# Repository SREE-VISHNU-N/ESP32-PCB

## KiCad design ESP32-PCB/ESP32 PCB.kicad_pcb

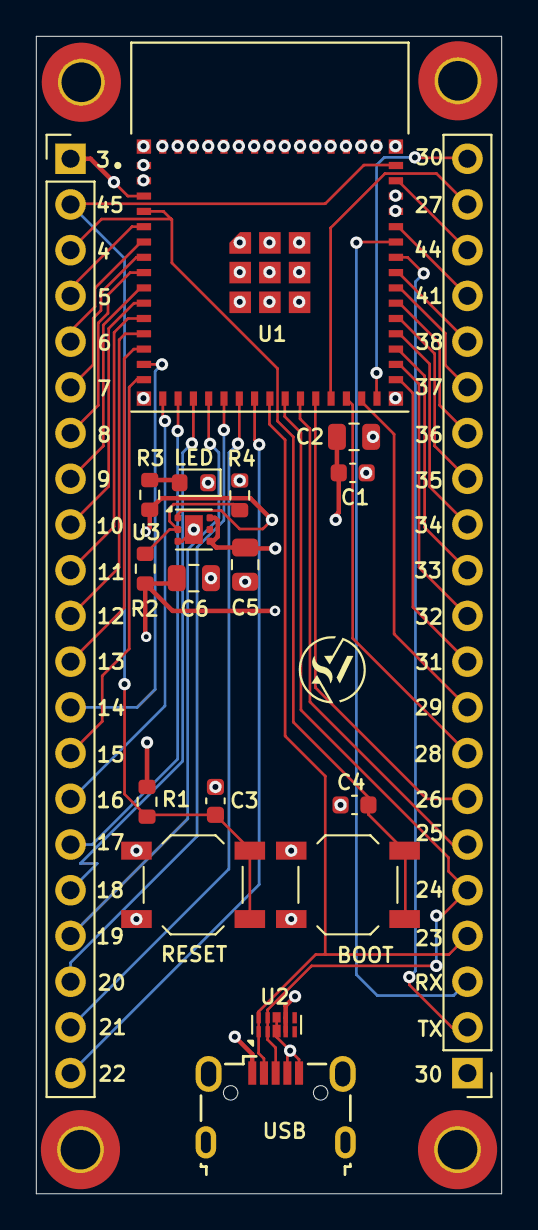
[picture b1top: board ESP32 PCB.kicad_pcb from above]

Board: 4 copper layers, 25.8 x 64.3 mm, 23 parts (0 on the bottom side), 45 nets.

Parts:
C1, C3, C4: 0.1uF; C_0603_1608Metric
C2, C5, C6: 10uF; C_0805_2012Metric
H1, H2, H3, H4: MountingHole_Pad; MountingHole_2.2mm_M2_Pad_TopBottom
J1, J2: Conn_01x21_Pin; PinHeader_1x21_P2.54mm_Vertical
LED: LED; LED_0603_1608Metric
R1: 10k; R_0603_1608Metric
R2: 1M; R_0603_1608Metric
R3: 5.1k; R_0603_1608Metric
R4: 200k; R_0603_1608Metric
RESET: RESET1; SW_SPST_TL3342
SW2: BOOT1; SW_SPST_TL3342
U1: ESP32-S3-MINI-1-N8; XCVR_ESP32-S3-MINI-1-N8
U2: D3V3XA4B10LP; Diodes_UDFN-10_1.0x2.5mm_P0.5mm
U3: TLV75801PDRV; WSON-6-1EP_2x2mm_P0.65mm_EP1x1.6mm
USB : USB_B_Micro; USB_Micro-B_Wuerth_629105150521

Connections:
/3V3: C1.1, C2.1, C6.1, J1.1, R1.1, R2.1, R3.1, U1.3 (3V3), U3.1 (OUT)
/5VUSB: C5.1, U2.4, U2.7 (NC), U3.4 (EN), U3.6 (IN), USB.1 (VBUS)
/EN: C3.1, J1.2, R1.2, RESET.3 (K), RESET.4 (A), U1.45 (EN)
/GP100: C4.1, J1.3, SW2.3 (K), SW2.4 (A), U1.4 (IO0)
/GP101: J1.4, U1.5 (IO1)
/GP102: J1.5, U1.6 (IO2)
/GP103: J1.6, U1.7 (IO3)
/GP104: J1.7, U1.8 (IO4)
/GP105: J1.8, U1.9 (IO5)
/GP106: J1.9, U1.10 (IO6)
/GP107: J1.10, U1.11 (IO7)
/GP108: J1.11, U1.12 (IO8)
/GP109: J1.12, U1.13 (IO9)
/GP1010: J1.13, U1.14 (IO10)
/GP1011: J1.14, U1.15 (IO11)
/GP1012: J1.15, U1.16 (IO12)
/GP1013: J1.16, U1.17 (IO13)
/GP1014: J1.17, U1.18 (IO14)
/GP1015: J1.18, U1.19 (IO15)
/GP1016: J1.19, U1.20 (IO16)
/GP1017: J1.20, U1.21 (IO17)
/GP1018: J1.21, U1.22 (IO18)
/GP1019: J2.4, U1.23 (IO19), U2.1, U2.10 (NC), USB.2 (D-)
/GP1020: J2.5, U1.24 (IO20), U2.2, U2.9 (NC), USB.3 (D+)
/GP1021: J2.6, U1.25 (IO21)
/GP1026: J2.7, U1.26 (IO26)
/GP1033: J2.8, U1.28 (IO33)
/GP1034: J2.9, U1.29 (IO34)
/GP1035: J2.10, U1.31 (IO35)
/GP1036: J2.11, U1.32 (IO36)
/GP1037: J2.12, U1.33 (IO37)
/GP1038: J2.13, U1.34 (IO38)
/GP1039: J2.14, U1.35 (IO39)
/GP1040: J2.15, U1.36 (IO40)
/GP1041: J2.16, U1.37 (IO41)
/GP1042: J2.17, U1.38 (IO42)
/GP1045: J2.18, U1.41 (IO45)
/GP1046: J2.19, U1.44 (IO46)
/GP1047: J2.20, U1.27 (IO47)
/GP1048: J2.21, U1.30 (IO48)
/RX: J2.3, U1.40 (RXD0)
/TX: J2.2, U1.39 (TXD0)
GND: C1.2, C2.2, C3.2, C4.2, C5.2, C6.2, H1.1, H2.1, H3.1, H4.1, J2.1, LED.1 (K), R4.2, RESET.1, RESET.2, SW2.1, SW2.2, U1.1 (GND), U1.2 (GND), U1.42 (GND), U1.43 (GND), U1.46 (GND), U1.47 (GND), U1.48 (GND), U1.49 (GND), U1.50 (GND), U1.51 (GND), U1.52 (GND), U1.53 (GND), U1.54 (GND), U1.55 (GND), U1.56 (GND), U1.57 (GND), U1.58 (GND), U1.59 (GND), U1.60 (GND), U1.61 (GND), U1.61_1 (GND), U1.61_2 (GND), U1.61_3 (GND), U1.61_4 (GND), U1.61_5 (GND), U1.61_6 (GND), U1.61_7 (GND), U1.61_8 (GND), U1.62 (GND), U1.63 (GND), U1.64 (GND), U1.65 (GND), U2.3 (VSS), U2.8 (VSS), U3.3 (GND), U3.7 (GND), USB.4 (ID), USB.5 (GND), USB.6 (Shield)
unnamed: LED.2 (A), R3.2
unnamed: R2.2, R4.1, U3.2 (FB)

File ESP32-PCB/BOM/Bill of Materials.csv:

"Reference","Value","Datasheet","Footprint","Qty","DNP"
"C1,C3,C4","0.1uF","~","Capacitor_SMD:C_0603_1608Metric","3",""
"C2,C5,C6","10uF","~","Capacitor_SMD:C_0805_2012Metric","3",""
"D1","LED","~","LED_SMD:LED_0603_1608Metric","1",""
"J1,J2","Conn_01x21_Pin","~","Connector_PinHeader_2.54mm:PinHeader_1x21_P2.54mm_Vertical","2",""
"J3","USB_B_Micro","~","Connector_USB:USB_Micro-B_Wuerth_629105150521","1",""
"R1","10k","~","Resistor_SMD:R_0603_1608Metric","1",""
"R2","1M","~","Resistor_SMD:R_0603_1608Metric","1",""
"R3","5.1k","~","Resistor_SMD:R_0603_1608Metric","1",""
"R4","200k","~","Resistor_SMD:R_0603_1608Metric","1",""
"SW1","RESET1","http://www.apem.com/int/index.php?controller=attachment&id_a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","SMD_Switch:SW_SPST_TL3342","1",""
"SW2","BOOT1","http://www.apem.com/int/index.php?controller=attachment&id_a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","SMD_Switch:SW_SPST_TL3342","1",""
"U1","ESP32-S3-MINI-1-N8","https://www.espressif.com/sites/default/files/documentation/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","ESP32-S3-MINI-1:XCVR_ESP32-S3-MINI-1-N8","1",""
"U2","D3V3XA4B10LP","https://www.diodes.com/assets/Datasheets/D3V3XA4B10LP.pdf","Package_DFN_QFN:Diodes_UDFN-10_1.0x2.5mm_P0.5mm","1",""
"U3","TLV75801PDRV","https://www.ti.com/lit/ds/symlink/tlv758p.pdf","Package_SON:WSON-6-1EP_2x2mm_P0.65mm_EP1x1.6mm","1",""

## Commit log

2025-02-24 Create ESP32
2025-02-24 Create Footprints
2025-02-24 Create Gerber
2025-02-24 Create Bom
